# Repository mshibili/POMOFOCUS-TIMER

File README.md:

# PomoFocus-Timer
Pomodoro produtivity timer along with fully functional clock and stop-watch.

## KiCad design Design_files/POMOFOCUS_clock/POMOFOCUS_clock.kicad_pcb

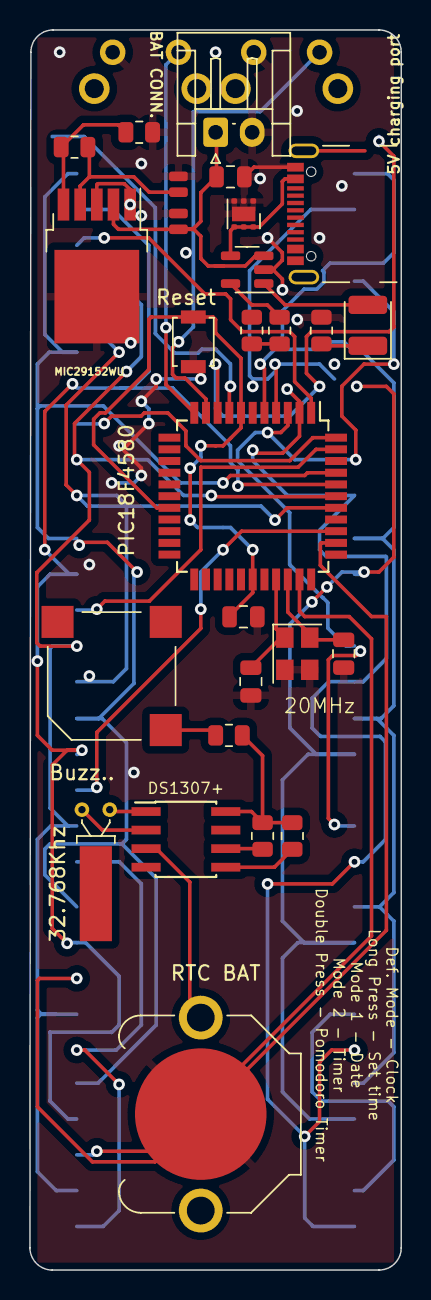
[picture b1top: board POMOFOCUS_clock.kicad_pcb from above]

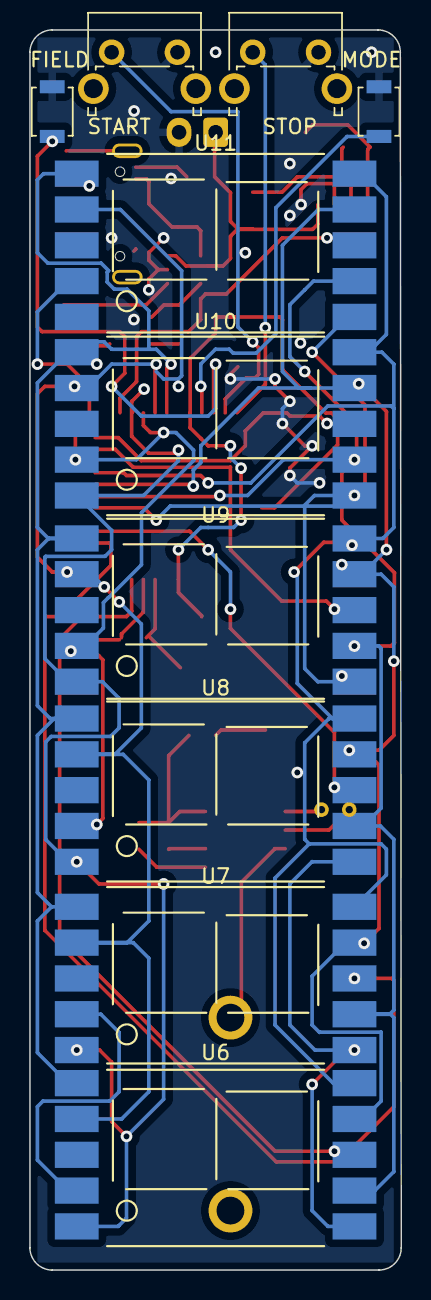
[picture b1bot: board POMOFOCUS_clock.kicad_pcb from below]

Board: 2 copper layers, 25.4 x 84.8 mm, 37 parts (10 on the bottom side), 36 nets.

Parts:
32.768Khz: 32.768Khz; Crystal_C26-LF_D2.1mm_L6.5mm_Horizontal_1EP_style1
BT1: Battery_Cell; BatteryHolder_Keystone_3001_1x12mm
BZ1: Buzzer; MagneticBuzzer_Kobitone_254-EMB84Q-RO
C1, C2: 0.1uf; C_0504_1310Metric
C3: 4.7uF; C_0805_2012Metric
C4, C5: C_Small; C_0805_2012Metric
C6: 0.1uf; C_0805_2012Metric
D1: LED; LED_1210_3225Metric
DS1307+: DS1307+; PowerIntegrations_SO-8
J1: USB_C_Receptacle_PowerOnly_6P; USB_C_Receptacle_GCT_USB4105-xx-A_16P_TopMnt_Horizontal
J2: Conn_01x02_Female; JST_EH_S2B-EH_1x02_P2.50mm_Horizontal
R1: 2.2K; R_0805_2012Metric
R2: 2.2k; R_0805_2012Metric
R3: 2.7k; R_0805_2012Metric
R4: 1.5k; R_0805_2012Metric
R5: 220R; R_0805_2012Metric
R7, R8, R9: R_Small; R_0805_2012Metric
SW1, SW2, SW4: SW_Push; SW_SPST_B3U-1000P
SW5, SW6: SW_Push; SW_Tactile_SPST_Angled_PTS645Vx39-2LFS
U1: MIC29152WU; TO-252-5_TabPin3
U2: TVS0500DRV; WSON-6-1EP_2x2mm_P0.65mm_EP1x1.6mm
U3: MCP73832-5-OT; SOT-23-5
U5: PIC18F4480-IP; TQFP-44_10x10mm_P0.8mm
U6, U7, U8, U9, U10, U11: KCSC02-136; 7SEGMENT-LED__HDSM531_HDSM533_SMD
Y1: 20Mhz; Crystal_SMD_3225-4Pin_3.2x2.5mm

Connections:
/A: U5.39 (C1IN-/PSP1/RD1), U6.7 (A), U7.7 (A), U8.7 (A), U9.7 (A), U10.7 (A), U11.7 (A)
/B: U5.38 (C1IN+/PSP0/RD0), U6.6 (B), U7.6 (B), U8.6 (B), U9.6 (B), U10.6 (B), U11.6 (B)
/BAT+: C1.1, C3.1, J2.1, U1.2 (VIN), U3.3 (VBAT)
/Buz: BZ1.2 (+), U5.17 (RB7/KBI3/PGD)
/C: U5.3 (P1B/PSP5/RD5), U6.4 (C), U7.4 (C), U8.4 (C), U9.4 (C), U10.4 (C), U11.4 (C)
/D: U5.4 (P1C/PSP6/RD6), U6.2 (D), U7.2 (D), U8.2 (D), U9.2 (D), U10.2 (D), U11.2 (D)
/DOWN/STOP: SW6.1, U5.11 (RB3/CANRX)
/DP: U5.2 (P1A/ECCP1/PSP4/RD4), U6.5 (DP), U7.5 (DP), U8.5 (DP), U9.5 (DP), U10.5 (DP), U11.5 (DP)
/E: U5.5 (P1D/PSP7/RD7), U6.1 (E), U7.1 (E), U8.1 (E), U9.1 (E), U10.1 (E), U11.1 (E)
/EN1: U5.32 (T13CKI/T1OSO/RC0), U6.8 (CC)
/EN2: U5.35 (T1OSI/RC1), U7.8 (CC)
/EN3: U5.36 (CCP1/RC2), U8.8 (CC)
/EN4: U5.43 (SDO/RC5), U9.8 (CC)
/EN5: U5.44 (CK/TX/RC6), U10.8 (CC)
/EN6: U5.1 (DT/RX/RC7), U11.8 (CC)
/F: U5.40 (C2IN+/PSP2/RD2), U6.9 (F), U7.9 (F), U8.9 (F), U9.9 (F), U10.9 (F), U11.9 (F)
/FIELD: SW4.1, U5.9 (RB1/INT1/AN8)
/G: U5.41 (C2IN-/PSP3/RD3), U6.10 (G), U7.10 (G), U8.10 (G), U9.10 (G), U10.10 (G), U11.10 (G)
/MODE: SW2.1, U5.8 (RB0/INT0/FLT0/AN10)
/UP/START: SW5.1, U5.10 (RB2/INT2/CANTX)
GND: BT1.2 (-), C1.2, C2.2, C3.2, C4.1, C5.1, C6.1, J1.A12 (GND), J2.2, R2.2, R4.2, R5.2, SW1.1, SW2.2, SW4.2, SW5.2, SW6.2, U1.1 (EN), U1.3 (GND), U2.1 (GND), U2.2 (GND), U2.3 (GND), U2.7 (GND), U3.2 (VSS), U5.6 (VSS), U5.29 (VSS), Y1.2, Y1.3
unnamed: BT1.1 (+), DS1307+.3 (VBAT)
unnamed: BZ1.1 (-), R9.1
unnamed: C4.2, U5.30 (OSC1/CLKI/RA7), Y1.1
unnamed: C5.2, U5.31 (OSC2/CLKO/RA6), Y1.4
unnamed: D1.1 (K), R5.1
unnamed: D1.2 (A), U3.1 (STAT)
unnamed: J1.A9 (VBUS), U2.4 (IN), U2.5 (IN), U2.6 (IN), U3.4 (VDD)
unnamed: R1.1, U3.5 (PROG)
unnamed: R1.2, R2.1
unnamed: R3.2, R4.1, U1.5 (ADJ)
unnamed: DS1307+.5 (SDA), R7.2
unnamed: DS1307+.6 (SCL), R8.2
unnamed: 32.768Khz.2, DS1307+.1 (X1)
unnamed: 32.768Khz.1, DS1307+.2 (X2)
VCC: C2.1, C6.2, DS1307+.8 (VCC), R3.1, R7.1, R8.1, R9.2, SW1.2, U1.4 (VOUT), U5.7 (VDD), U5.18 (~MCLR/VPP/RE3), U5.28 (VDD)

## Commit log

2023-01-17 Repo. Migration Update
